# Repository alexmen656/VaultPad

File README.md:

# Hackpad

This is just a little macropad with 4 buttons that I put together.

The 4 buttons do these things:
- Screenshot tool (takes selective screenshots)
- Developer combo (opens terminal + VS Code)
- Emoji picker (for quick reactions)
- Media control + focus mode toggle

**Bonus:** There's also a small storage compartment inside for SD cards, USB sticks, or other tiny accessories.

## How this thing came together
Made the 3D model in Fusion 360 and imported the PCB from KiCAD. The microcontroller is on the back so it looks cleaner from the front. Pretty happy with how it turned out.
 
| 1. Image   | 2. Image  |
|------------|-----------|
|  |  |
|  |  |

## The PCB
Designed in KiCAD, was a bit tedious but it works. Here are some screenshots:

| 1. Image   | 2. Image  |
|------------|-----------|
|  |  |

## BOM
1x XIAO RP2040 \
4x Cherry MX switches \
4x SK6812 MINI-E LEDs \
4x Heatset inserts (M3x5x4) \
4x screws (M3x16) \
3d printing Filament

## Make your own Hackpad!
Want to build one yourself? Check out this guide: https://hackpad.hackclub.com/guide

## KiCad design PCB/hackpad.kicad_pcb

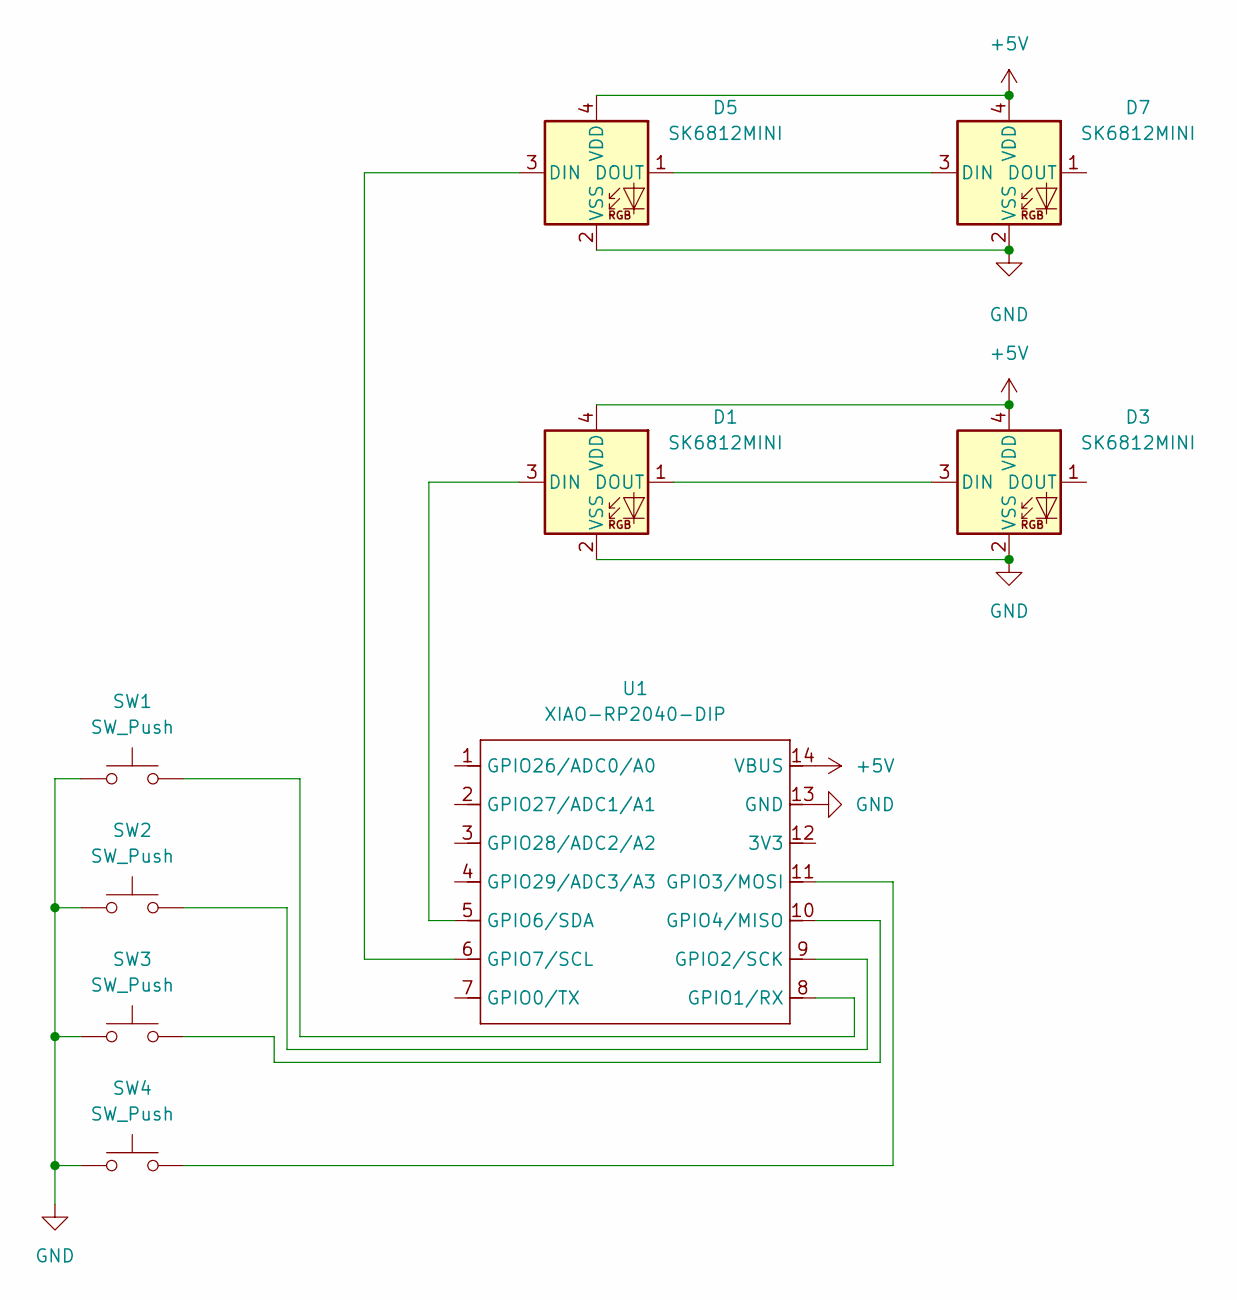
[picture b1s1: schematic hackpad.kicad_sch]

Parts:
D1, D3, D5, D7: SK6812MINI; LED_SK6812MINI_PLCC4_3.5x3.5mm_P1.75mm
SW1, SW2, SW3, SW4: SW_Push; SW_Cherry_MX_1.00u_PCB
U1: XIAO-RP2040-DIP

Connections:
+5V: D1.4 (VDD), D3.4 (VDD), D5.4 (VDD), D7.4 (VDD), U1.14 (VBUS)
GND: D1.2 (VSS), D3.2 (VSS), D5.2 (VSS), D7.2 (VSS), SW1.1, SW2.1, SW3.1, SW4.1, U1.13 (GND)
unnamed: D1.3 (DIN), U1.5 (GPIO6/SDA)
unnamed: D1.1 (DOUT), D3.3 (DIN)
unnamed: D5.3 (DIN), U1.6 (GPIO7/SCL)
unnamed: D5.1 (DOUT), D7.3 (DIN)
unnamed: SW1.2, U1.8 (GPIO1/RX)
unnamed: SW2.2, U1.9 (GPIO2/SCK)
unnamed: SW4.2, U1.11 (GPIO3/MOSI)
unnamed: SW3.2, U1.10 (GPIO4/MISO)

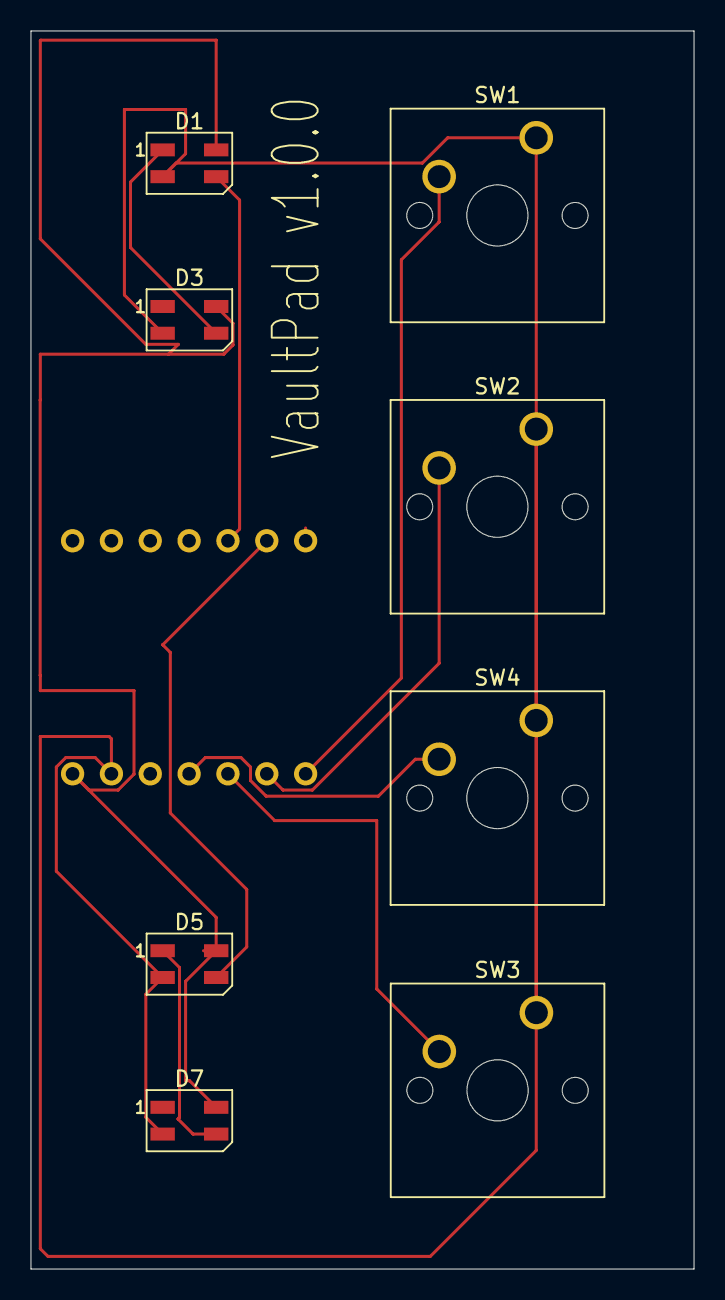
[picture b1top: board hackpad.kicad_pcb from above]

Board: 2 copper layers, 43.4 x 81.0 mm, 9 parts (1 on the bottom side), 10 nets.

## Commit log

2025-07-09 Init
2025-07-09 add screenshots
2025-07-10 new pcb
2025-07-10 new screenshots
